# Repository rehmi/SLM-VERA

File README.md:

# SLM-VERA
An interface board for working with the AAXA VERA SLM controller

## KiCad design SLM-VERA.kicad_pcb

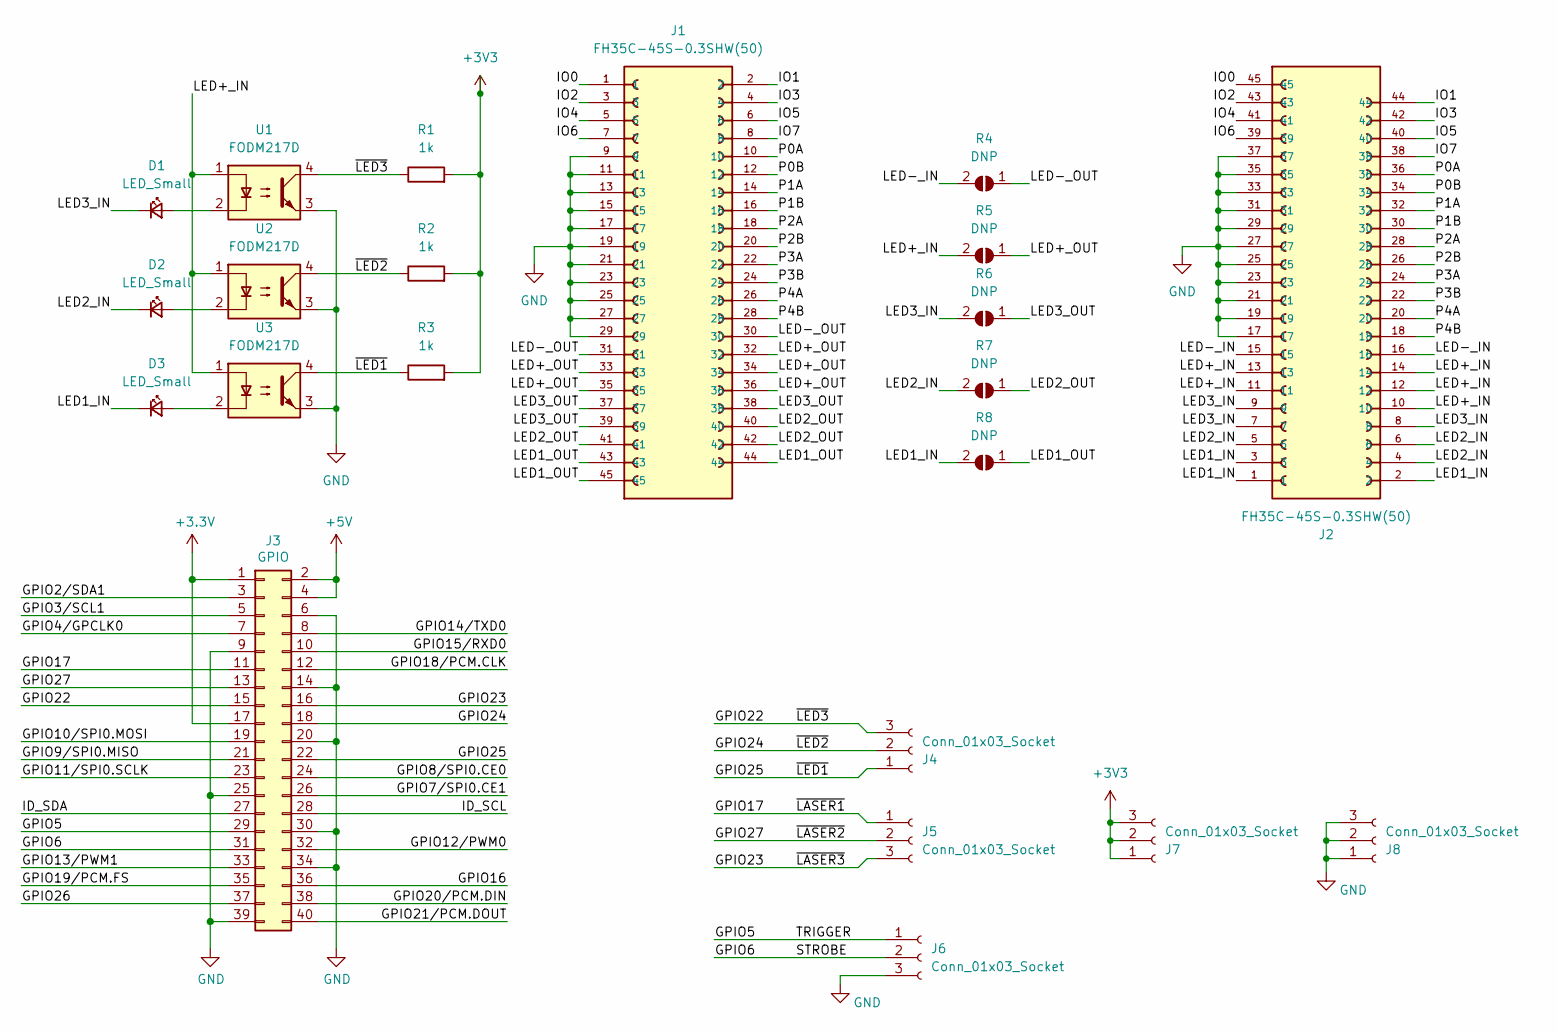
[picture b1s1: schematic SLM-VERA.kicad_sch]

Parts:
D1, D2, D3: LED_Small; LED_1206_3216Metric_Pad1.42x1.75mm_HandSolder
J1, J2: FH35C-45S-0.3SHW(50); HRS_FH35C-45S-0.3SHW(50); PARTREV 14.12.17
J3: GPIO; PinSocket_2x20_P2.54mm_Vertical
J4, J5, J6, J7, J8: Conn_01x03_Socket; PinSocket_1x03_P2.54mm_Vertical_SMD_Pin1Right
R1, R2, R3: 1k; R_1206_3216Metric_Pad1.30x1.75mm_HandSolder
R4, R5, R6, R7, R8: DNP; R_0402_1005Metric
U1, U2, U3: FODM217D; SOP-4_4.4x2.6mm_P1.27mm

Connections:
+5V: J3.2, J3.4
/GPIO2/SDA1: J3.3
/GPIO3/SCL1: J3.5
/GPIO4/GPCLK0: J3.7
/GPIO5: J3.29, J6.1
/GPIO6: J3.31, J6.2
/GPIO7/SPI0.CE1: J3.26
/GPIO8/SPI0.CE0: J3.24
/GPIO9/SPI0.MISO: J3.21
/GPIO10/SPI0.MOSI: J3.19
/GPIO11/SPI0.SCLK: J3.23
/GPIO12/PWM0: J3.32
/GPIO13/PWM1: J3.33
/GPIO14/TXD0: J3.8
/GPIO15/RXD0: J3.10
/GPIO16: J3.36
/GPIO17: J3.11, J5.1
/GPIO18/PCM.CLK: J3.12
/GPIO19/PCM.FS: J3.35
/GPIO20/PCM.DIN: J3.38
/GPIO21/PCM.DOUT: J3.40
/GPIO22: J3.15, J4.3, R1.1, U1.4
/GPIO23: J3.16, J5.3
/GPIO24: J3.18, J4.2, R2.1, U2.4
/GPIO25: J3.22, J4.1, R3.1, U3.4
/GPIO26: J3.37
/GPIO27: J3.13, J5.2
/ID_SCL: J3.28
/ID_SDA: J3.27
/IO0: J1.1, J2.45
/IO1: J1.2, J2.44
/IO2: J1.3, J2.43
/IO3: J1.4, J2.42
/IO4: J1.5, J2.41
/IO5: J1.6, J2.40
/IO6: J1.7, J2.39
/IO7: J1.8, J2.38
/LED1_IN: D3.1 (K), J2.1, J2.2, J2.3, R8.2 (B)
/LED1_OUT: J1.43, J1.44, J1.45, R8.1 (A)
/LED2_IN: D2.1 (K), J2.4, J2.5, J2.6, R7.2 (B)
/LED2_OUT: J1.40, J1.41, J1.42, R7.1 (A)
/LED3_IN: D1.1 (K), J2.7, J2.8, J2.9, R6.2 (B)
/LED3_OUT: J1.37, J1.38, J1.39, R6.1 (A)
/LED+_IN: J2.10, J2.11, J2.12, J2.13, J2.14, R5.2 (B), U1.1, U2.1, U3.1
/LED+_OUT: J1.32, J1.33, J1.34, J1.35, J1.36, R5.1 (A)
/LED-_IN: J2.15, J2.16, R4.2 (B)
/LED-_OUT: J1.30, J1.31, R4.1 (A)
/P0A: J1.10, J2.36
/P0B: J1.12, J2.34
/P1A: J1.14, J2.32
/P1B: J1.16, J2.30
/P2A: J1.18, J2.28
/P2B: J1.20, J2.26
/P3A: J1.22, J2.24
/P3B: J1.24, J2.22
/P4A: J1.26, J2.20
/P4B: J1.28, J2.18
GND: J1.9, J1.11, J1.13, J1.15, J1.17, J1.19, J1.21, J1.23, J1.25, J1.27, J1.29, J2.17, J2.19, J2.21, J2.23, J2.25, J2.27, J2.29, J2.31, J2.33, J2.35, J2.37, J3.6, J3.9, J3.14, J3.20, J3.25, J3.30, J3.34, J3.39, J6.3, J8.1, J8.2, J8.3, U1.3, U2.3, U3.3
unnamed: D1.2 (A), U1.2
unnamed: D2.2 (A), U2.2
unnamed: D3.2 (A), U3.2

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
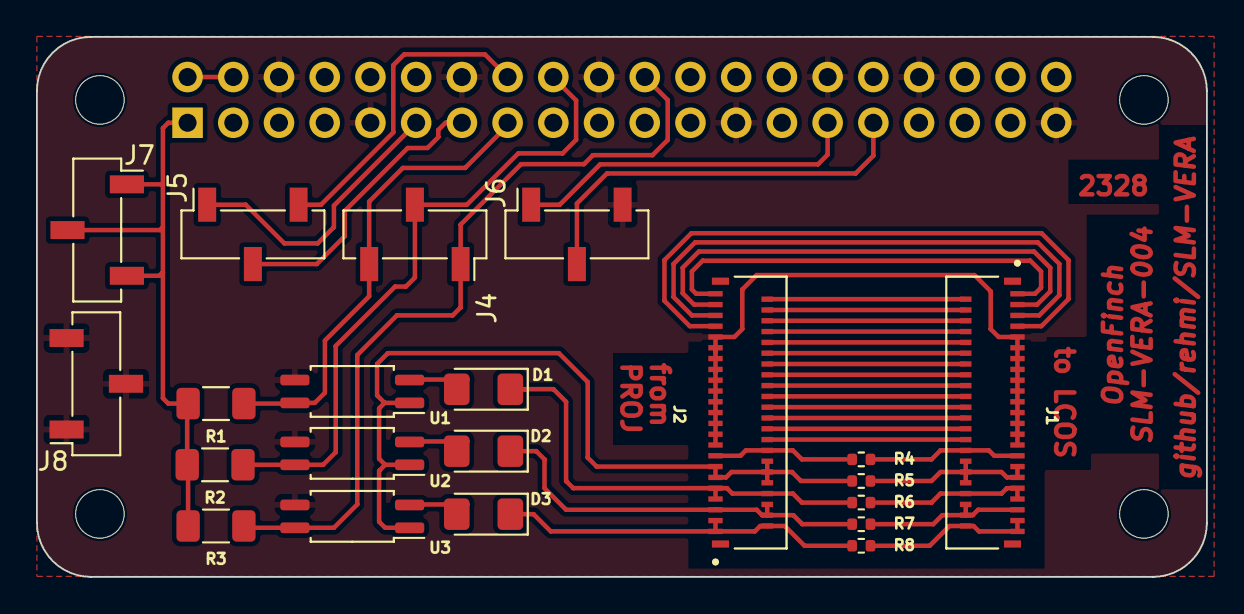
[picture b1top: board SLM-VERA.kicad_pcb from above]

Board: 2 copper layers, 65.0 x 30.0 mm, 26 parts (1 on the bottom side), 42 nets.

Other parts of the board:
MH1, MH2, MH3, MH4: MountingHole_2.7mm_M2.5

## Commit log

2023-06-28 initial commit of SLM-VERA-001 unfortunately, the FFC connectors are rotated 180º
2023-06-28 SLM-VERA-002: fixed J1 & J2; all routes on top copper
2023-06-29 SLM-VERA-002: updated gerbers
2023-07-09 changed ESP32-Devkit-C to Seeeduino Xiao
2023-07-10 Redesigned as Raspberry Pi (Zero) hat
2023-07-24 updated R1-R3 values to 1k on SLM-VERA-004
